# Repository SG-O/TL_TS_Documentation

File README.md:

# TL_TS_Documentation
A collection of findings, documentation, and practical insights into the IBM TS3200 tape library and potentially its siblings based on the BDT FlexStor II platform.

## Default passwords
A list of default passwords (including undocumented ones) can be [found here](passwords.txt).

## Dummy iSCSI card
A dummy card for the iSCSI slot is [available here](Dummy_iSCSI_PCB/). It also includes the pinout of the service serial port (RJ14).

## Cross flashing firmware
Instructions for crossflashing firmware can be [found here](https://www.reddit.com/r/DataHoarder/comments/167xd5o/howto_crossflashing_firmware_on_2448bay_lto/).

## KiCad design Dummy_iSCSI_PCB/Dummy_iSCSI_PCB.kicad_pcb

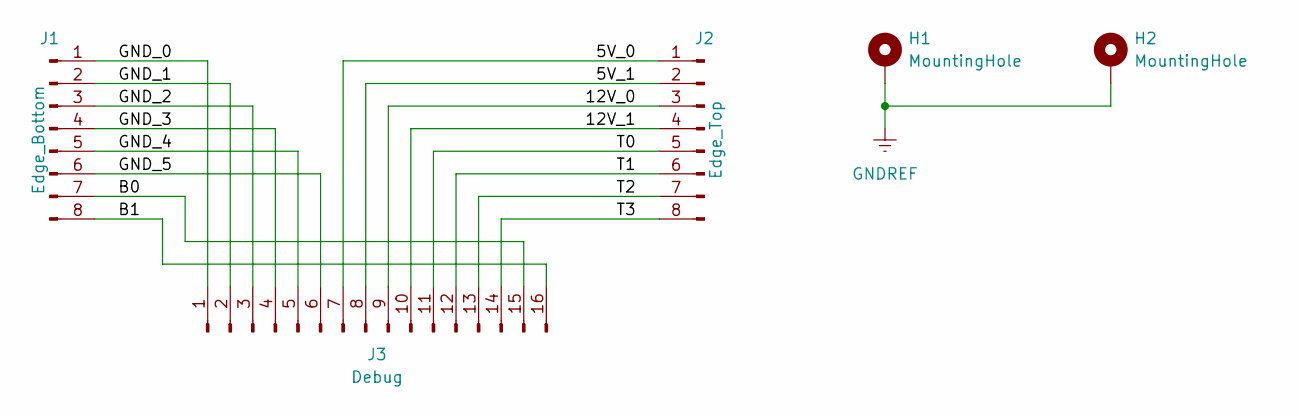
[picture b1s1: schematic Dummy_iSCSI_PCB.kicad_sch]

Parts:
H1, H2: MountingHole; MountingHole_3.2mm_M3_ISO7380_Pad
J1: Edge_Bottom
J2: Edge_Top
J3: Debug; PinHeader_1x16_P2.54mm_Vertical

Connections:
/5V_0: J2.1, J3.7
/5V_1: J2.2, J3.8
/12V_0: J2.3, J3.9
/12V_1: J2.4, J3.10
/B0: J1.7, J3.15
/B1: J1.8, J3.16
/GND_0: J1.1, J3.1
/GND_1: J1.2, J3.2
/GND_2: J1.3, J3.3
/GND_3: J1.4, J3.4
/GND_4: J1.5, J3.5
/GND_5: J1.6, J3.6
/T0: J2.5, J3.11
/T1: J2.6, J3.12
/T2: J2.7, J3.13
/T3: J2.8, J3.14
GNDREF: H1.1, H2.1

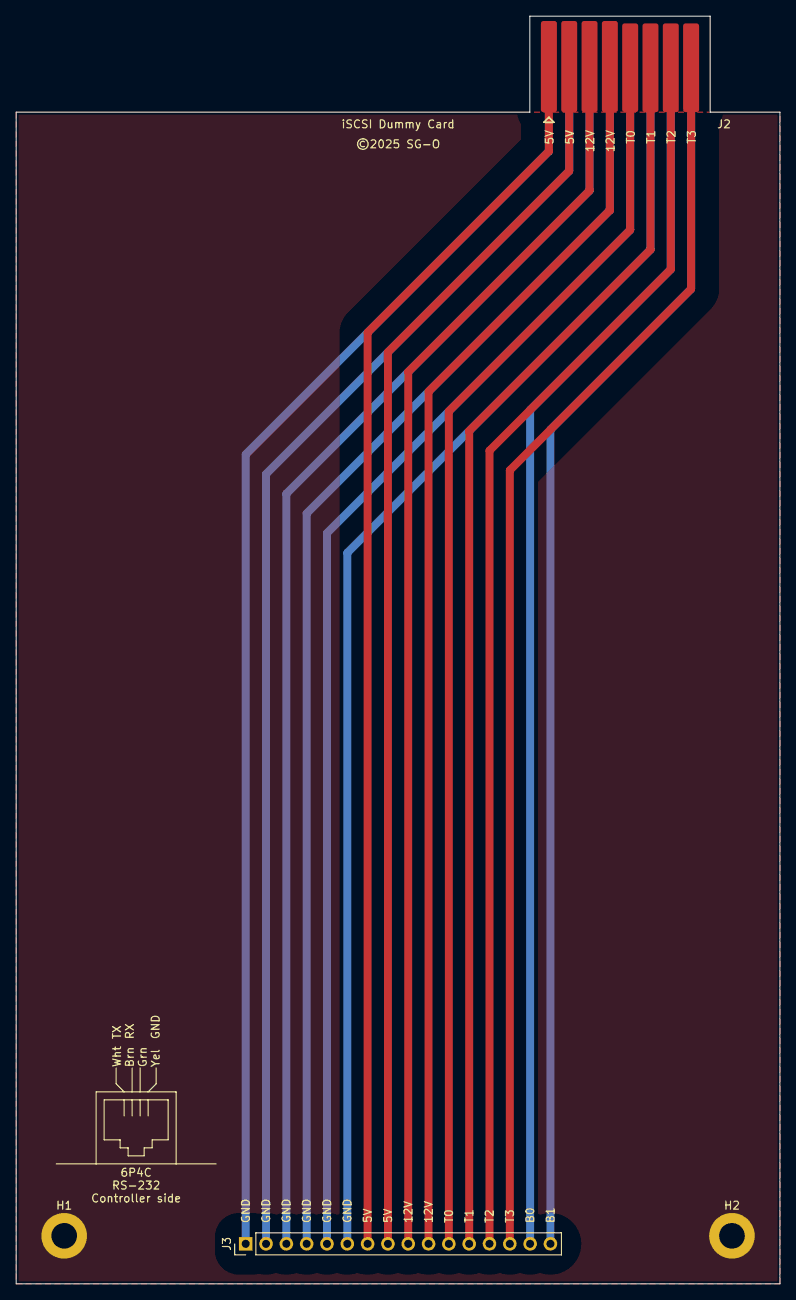
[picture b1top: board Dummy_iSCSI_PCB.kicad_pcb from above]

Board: 2 copper layers, 95.5 x 158.5 mm, 5 parts (0 on the bottom side), 17 nets.

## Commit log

2025-07-21 fixed readme
2025-07-21 added cross flashing instructions

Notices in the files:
Dummy_iSCSI_PCB/Dummy_iSCSI_PCB.kicad_pcb:
©2025 SG-O
